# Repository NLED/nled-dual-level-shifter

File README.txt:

THERE IS NO WARRANTY FOR THE PROGRAM, TO THE EXTENT PERMITTED BY APPLICABLE LAW. 
EXCEPT WHEN OTHERWISE STATED IN WRITING THE COPYRIGHT HOLDERS AND/OR OTHER PARTIES 
PROVIDE THE PROGRAM AS IS WITHOUT WARRANTY OF ANY KIND, EITHER EXPRESSED OR IMPLIED,
INCLUDING, BUT NOT LIMITED TO, THE IMPLIED WARRANTIES OF MERCHANTABILITY AND FITNESS 
FOR A PARTICULAR PURPOSE. THE ENTIRE RISK AS TO THE QUALITY AND PERFORMANCE OF THE 
PROGRAM IS WITH YOU. SHOULD THE PROGRAM PROVE DEFECTIVE, YOU ASSUME THE COST OF ALL 
NECESSARY SERVICING, REPAIR OR CORRECTION.

 Original Author: Jeffrey Nygaard
 Company: Northern Lights Electronic Design, LLC
 Date: March 5, 2018
 Contact: JNygaard@NLEDshop.com
 Copyright© 2018 by Northern Lights Electronic Design, LLC. All Rights Reserved
 
;=============          www.NLEDShop.com/addoncards           ============
;=============     www.NorthernLightsElectronicDesign.com       ============

This work is licensed under a Attribution-NonCommercial 4.0 International (CC BY-NC 4.0)
https://creativecommons.org/licenses/by-nc/4.0/legalcode

Free to use for personal use, but please attribute the original author.

Commercial licenses versions are available for a donation of any amount. Contact JNygaard@NLEDshop.com for details.

================================================================================================================

Ready-made devices are available for purchase, and large batch manufacturing of any device can be requested.
Please see the webpage www.NLEDShop.com/pixelproducts

NLED is available for custom design and manufacturing, please contact via phone or email to discuss your project.

================================================================================================================

This dual channel level translator(shifter) is used to convert 3.3 volt signals to 5 volt signals. It features 
on-board low drop out linear regulators for both the 5 volt and 3.3 volt rails. That allows it to support a VIN 
of up to 12 volts, which makes it easy to connect to other devices. The TXS0102 I.C. allows speeds up to 24Mbps, 
designed specifically for addressable LED pixels which utilize clock and data lines, or other types of SPI based 
communication. The layout of the board allows it to be used inline with standard wiring for adressable pixels, 
no tricky wiring or jumping.

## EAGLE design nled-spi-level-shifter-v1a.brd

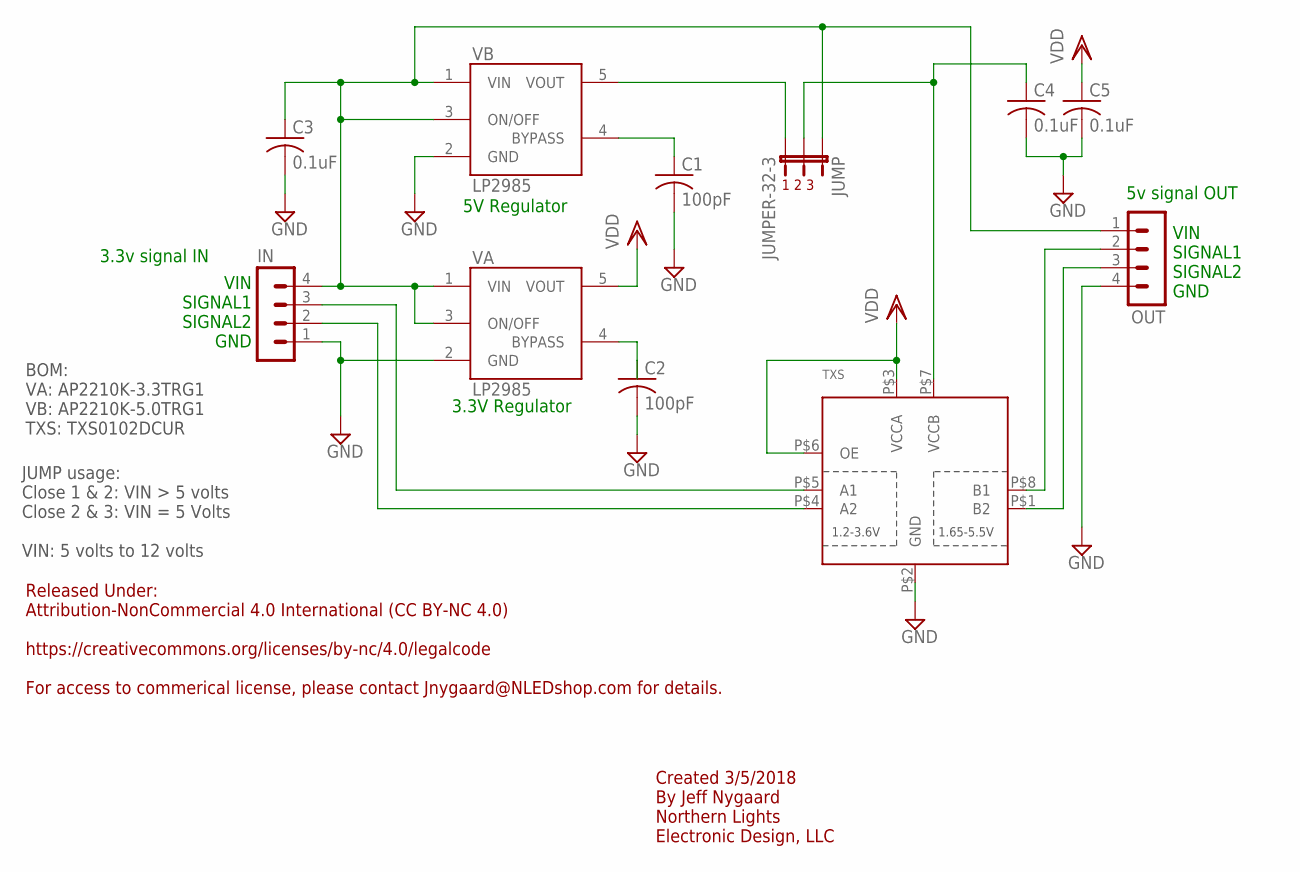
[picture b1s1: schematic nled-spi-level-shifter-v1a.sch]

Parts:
C1, C2: 100pF; C0805
C3, C4, C5: 0.1uF; C0805
IN: MA04-1
JUMP: JUMPER-32-3; SJ_3_PASTE2&3
OUT: MA04-1
TXS: TXS0102; VFSOP-8
VA: LP2985AIM5-3.3; SOT25
VB: LP2985AIM5-3.3; SOT25

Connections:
BYPASS: C1.1, VB.4 (BYPASS)
BYPASSB: C2.1, VA.4 (BYPASS)
GND: C1.2, C2.2, C3.2, C4.2, C5.2, IN.1, OUT.4, TXS.P$2 (GND), VA.2 (GND), VB.2 (GND)
unnamed: C4.1, JUMP.2, TXS.P$7 (VCCB)
unnamed: IN.3, TXS.P$5 (A1)
unnamed: IN.2, TXS.P$4 (A2)
unnamed: OUT.2, TXS.P$8 (B1)
unnamed: OUT.3, TXS.P$1 (B2)
unnamed: JUMP.3, VB.5 (VOUT)
VDD: C5.1, TXS.P$3 (VCCA), TXS.P$6 (OE), VA.5 (VOUT)
VIN: C3.1, IN.4, JUMP.1, OUT.1, VA.1 (VIN), VA.3 (ON/OFF), VB.1 (VIN), VB.3 (ON/OFF)

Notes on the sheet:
3.3v signal IN
5v signal OUT
Released Under: Attribution-NonCommercial 4.0 International (CC BY-NC 4.0) https://creativecommons.org/licenses/by-nc/4.0/legalcode For access to commerical license, please contact Jnygaard@NLEDshop.com for details.
Created 3/5/2018 By Jeff Nygaard Northern Lights Electronic Design, LLC
3.3V Regulator
5V Regulator
1 2 3
JUMP usage: Close 1 & 2: VIN > 5 volts Close 2 & 3: VIN = 5 Volts VIN: 5 volts to 12 volts
BOM: VA: AP2210K-3.3TRG1 VB: AP2210K-5.0TRG1 TXS: TXS0102DCUR
VIN SIGNAL1 SIGNAL2 GND

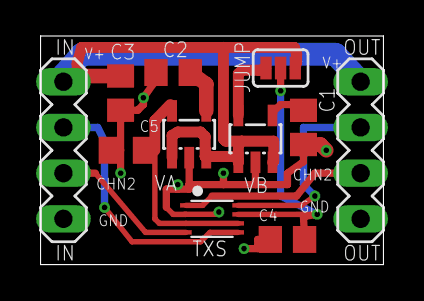
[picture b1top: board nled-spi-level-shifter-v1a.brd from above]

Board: 2 copper layers, 19.1 x 12.7 mm, 11 parts (0 on the bottom side), 11 nets.

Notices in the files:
parts and their libraries:
SparkFun: Licensing: CC v3.0 Share-Alike You are welcome to use this library for commercial purposes.
